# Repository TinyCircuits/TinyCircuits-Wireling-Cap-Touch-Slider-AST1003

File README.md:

# TinyCircuits Wireling Cap Touch Slider
# AST1003 Rev1

The design files are located under design_files/ for the TinyCircuits AST1003 Rev 1 PCB. This is a Wireling board which detects the presence and location of conductive materials such as a user's finger.  Includes a built-in microcontroller to perform the capacitance measurements.

Format is in Cadsoft Eagle format - Eagle version 6.2 was used for the original design.

For more infomation on this, check out the product page at TinyCircuits.com

# License:

Design by TinyCircuits.
All design files are released under the Creative Commons Attribution Share-Alike 3.0 License, see the following link for details: http://creativecommons.org/licenses/by-sa/3.0

All text above must be included in any redistribution or derived design

This project uses designs and concepts developed as part of the Arduino project and the LilyPad project.  The TinyCircuits design files themselves (schematics, PCB and libraries) are not directly derived from these works' design files and have been created new, however the concepts and basic architecture behind the TinyDuino and TinyLily products are derived and we thank the hard work of the organizations below for their contributions to open-source hardware:
  
Original Arduino Uno Design by Team Arduino

LilyPad Arduino Design by Leah Buechley and Sparkfun Electronics

Please support the open-source hardware community

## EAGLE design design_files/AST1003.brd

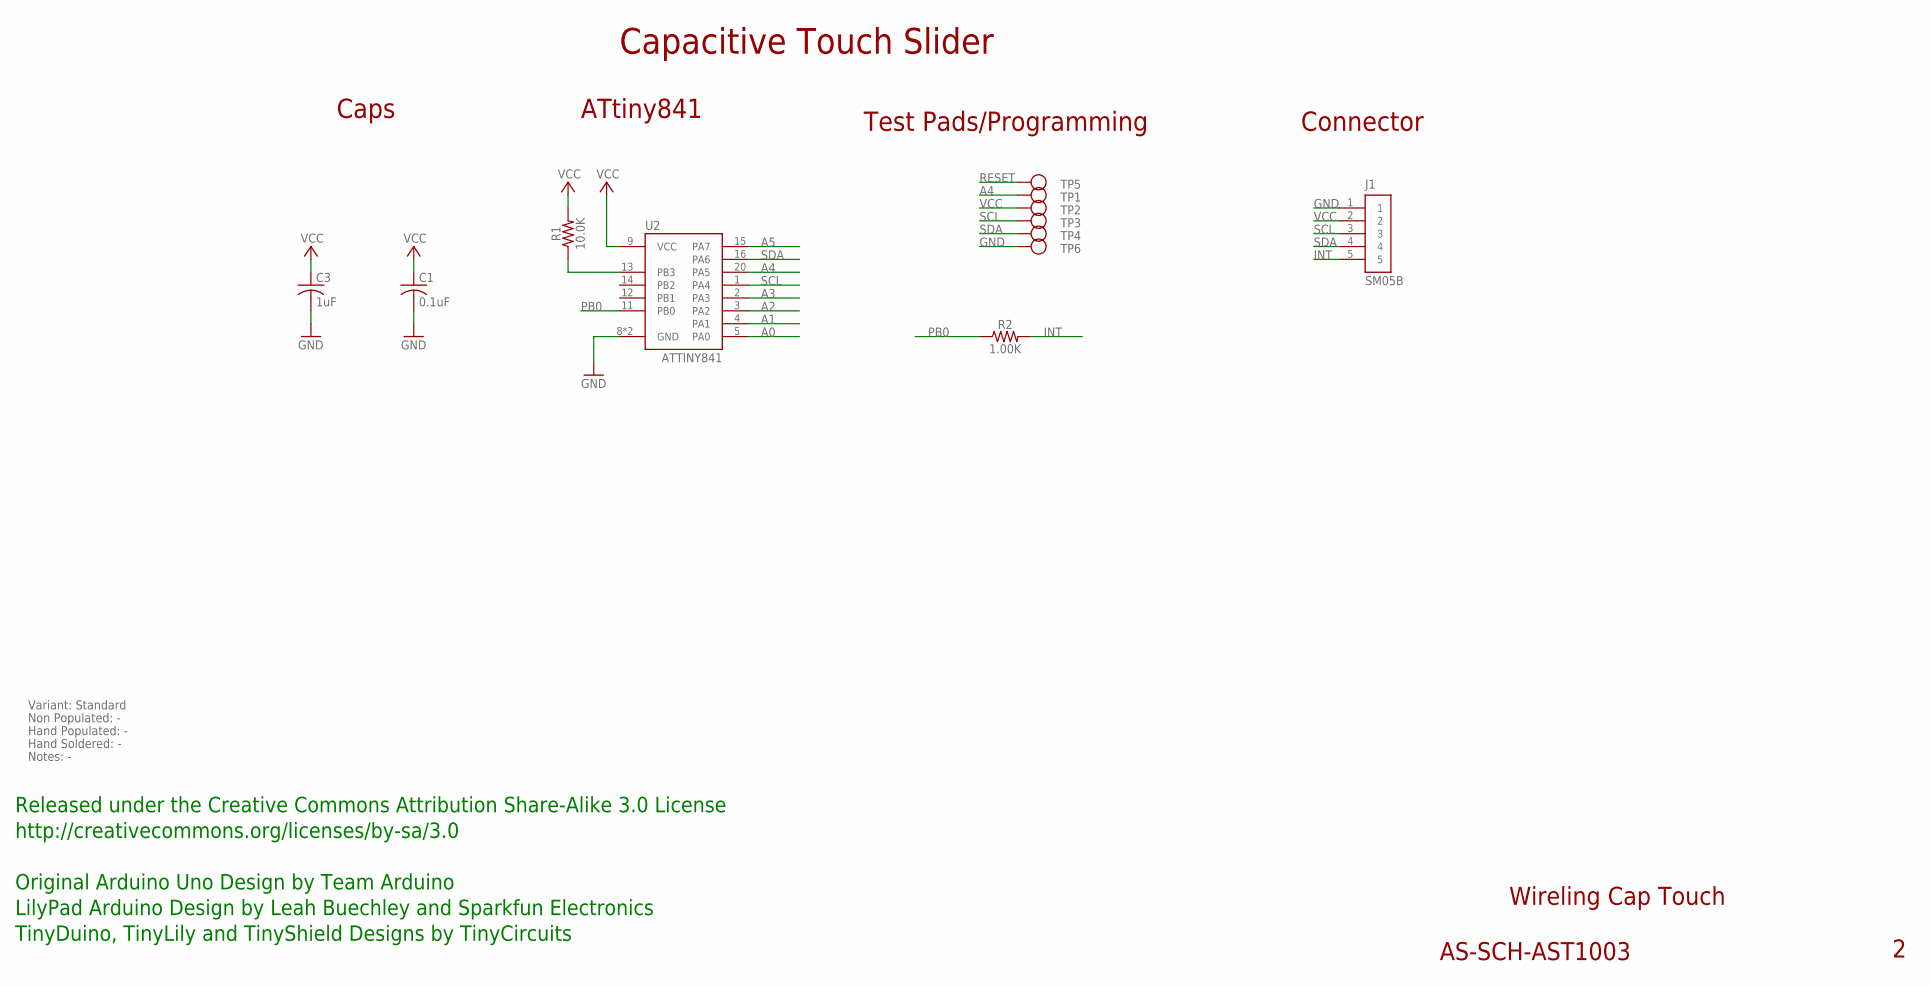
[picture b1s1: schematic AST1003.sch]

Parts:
C1: 0.1uF; C0402
C3: 1uF; C0603; PARTNO AS-ITM-00410
J1: SM05B; JST_SH_5X1
R1: 10.0K; 0402
R2: 1.00K; 0402; PARTNO AS-ITM-00003
TP1, TP2, TP3, TP4, TP5, TP6: TEST_POINT; TEST_POINT_1MM
U2: ATTINY841; VQFN-20

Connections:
A0: U2.5 (PA0)
A1: U2.4 (PA1)
A2: U2.3 (PA2)
A3: U2.2 (PA3)
A4: TP1.P$1, U2.20 (PA5)
A5: U2.15 (PA7)
GND: C1.2, C3.2, J1.1, TP6.P$1, U2.8 (GND), U2.PAD (GND)
INT: J1.5, R2.2
PB0: R2.1, U2.11 (PB0)
RESET: R1.1, TP5.P$1, U2.13 (PB3)
SCL: J1.3, TP3.P$1, U2.1 (PA4)
SDA: J1.4, TP4.P$1, U2.16 (PA6)
VCC: C1.1, C3.1, J1.2, R1.2, TP2.P$1, U2.9 (VCC)

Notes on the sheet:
Wireling Cap Touch
AS-SCH-AST1003
Capacitive Touch Slider
Released under the Creative Commons Attribution Share-Alike 3.0 License
http://creativecommons.org/licenses/by-sa/3.0
Original Arduino Uno Design by Team Arduino
TinyDuino, TinyLily and TinyShield Designs by TinyCircuits
LilyPad Arduino Design by Leah Buechley and Sparkfun Electronics
Test Pads/Programming
ATtiny841
Caps
Connector
Non Populated: -
Hand Populated: -
Hand Soldered: -
Variant: Standard
Notes: -

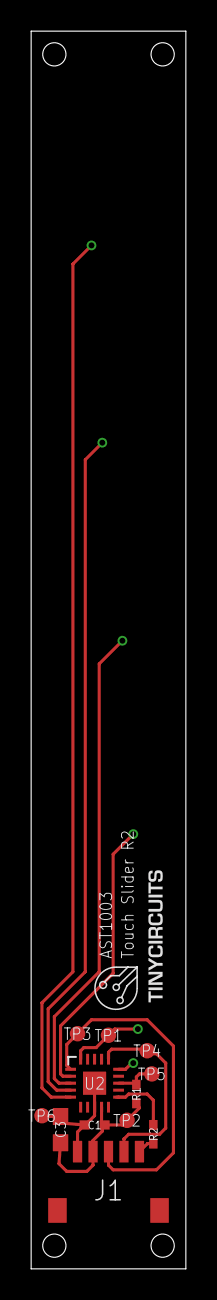
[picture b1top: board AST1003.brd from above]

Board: 2 copper layers, 10.0 x 80.0 mm, 13 parts (0 on the bottom side), 8 nets.

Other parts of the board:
U$1: DOCFIELD-TINYCIRCUITS-PCB

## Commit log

2019-12-17 updated documentation
2020-01-15 images
2020-01-15 this nnaming system gets me
2020-01-16 datasheet
2020-02-04 mass image update
2020-04-15 image of output
2020-08-14 Add CAD data
